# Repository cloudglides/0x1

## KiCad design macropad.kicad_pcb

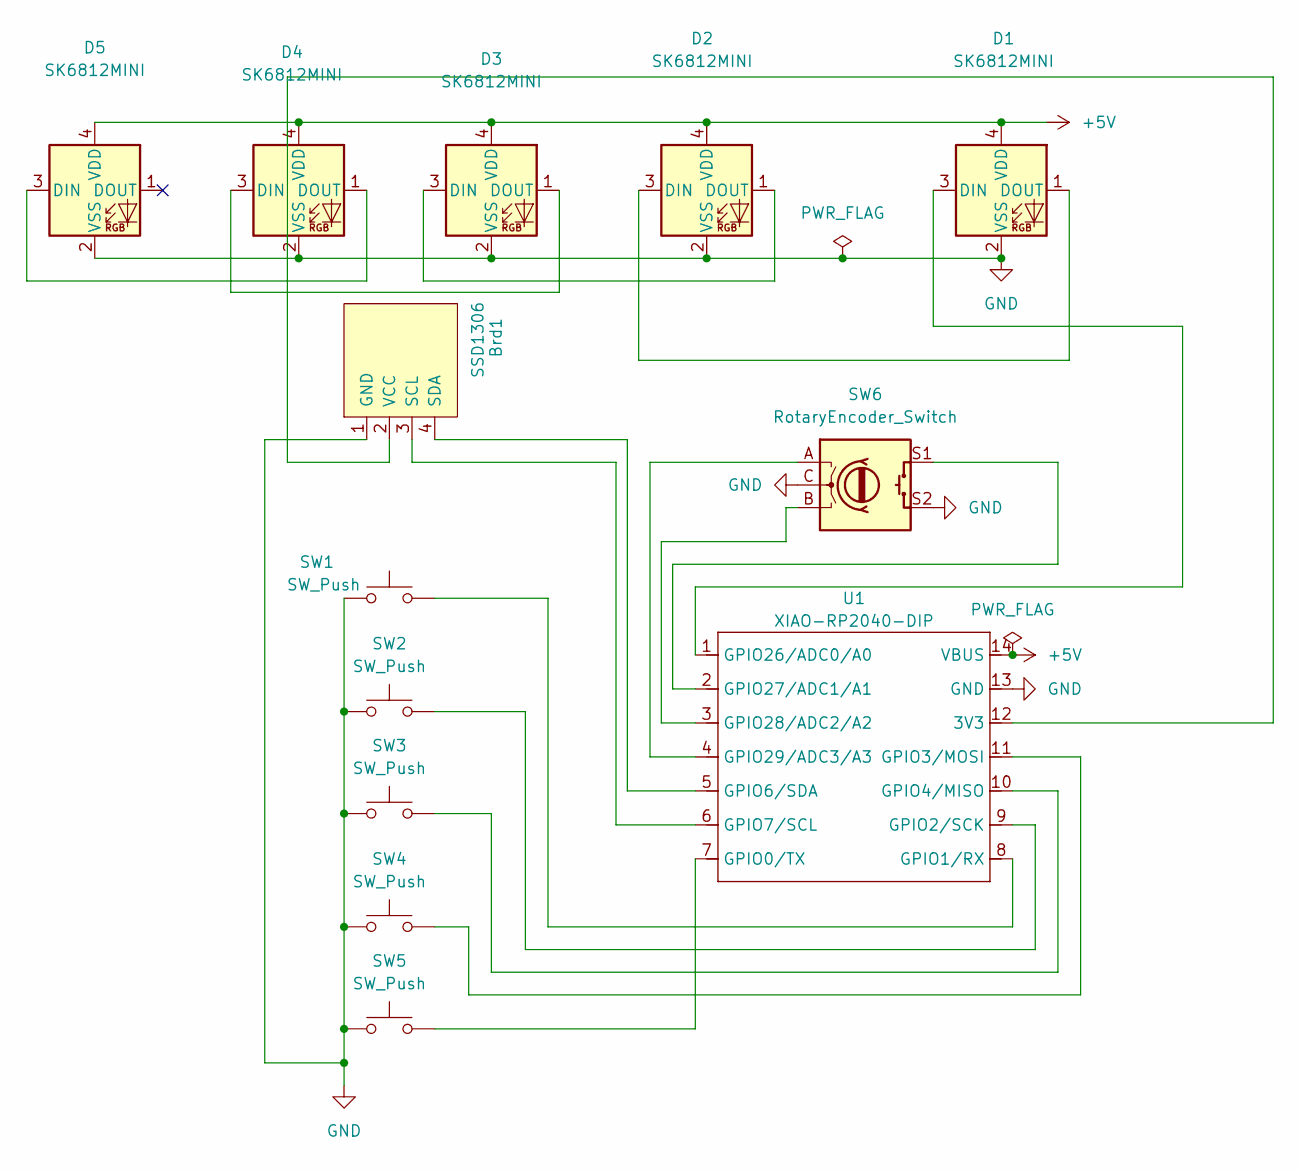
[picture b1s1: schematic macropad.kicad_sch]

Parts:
Brd1: SSD1306; SSD1306-0.91-OLED-4pin-128x32
D1, D2, D3, D4, D5: SK6812MINI; LED_SK6812MINI_PLCC4_3.5x3.5mm_P1.75mm
SW1, SW2, SW3, SW4, SW5: SW_Push; SW_Cherry_MX_1.00u_PCB
SW6: RotaryEncoder_Switch; RotaryEncoder_Alps_EC11E-Switch_Vertical_H20mm
U1: XIAO-RP2040-DIP

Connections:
+5V: D1.4 (VDD), D2.4 (VDD), D3.4 (VDD), D4.4 (VDD), D5.4 (VDD), U1.14 (VBUS)
GND: Brd1.1 (GND), D1.2 (VSS), D2.2 (VSS), D3.2 (VSS), D4.2 (VSS), D5.2 (VSS), SW1.1, SW2.1, SW3.1, SW4.1, SW5.1, SW6.C, SW6.S2, U1.13 (GND)
unnamed: Brd1.3 (SCL), U1.6 (GPIO7/SCL)
unnamed: Brd1.4 (SDA), U1.5 (GPIO6/SDA)
unnamed: Brd1.2 (VCC), U1.12 (3V3)
unnamed: D1.3 (DIN), U1.1 (GPIO26/ADC0/A0)
unnamed: D1.1 (DOUT), D2.3 (DIN)
unnamed: D2.1 (DOUT), D3.3 (DIN)
unnamed: D3.1 (DOUT), D4.3 (DIN)
unnamed: D4.1 (DOUT), D5.3 (DIN)
unnamed: SW5.2, U1.7 (GPIO0/TX)
unnamed: SW1.2, U1.8 (GPIO1/RX)
unnamed: SW2.2, U1.9 (GPIO2/SCK)
unnamed: SW4.2, U1.11 (GPIO3/MOSI)
unnamed: SW3.2, U1.10 (GPIO4/MISO)
unnamed: SW6.S1, U1.2 (GPIO27/ADC1/A1)
unnamed: SW6.B, U1.3 (GPIO28/ADC2/A2)
unnamed: SW6.A, U1.4 (GPIO29/ADC3/A3)

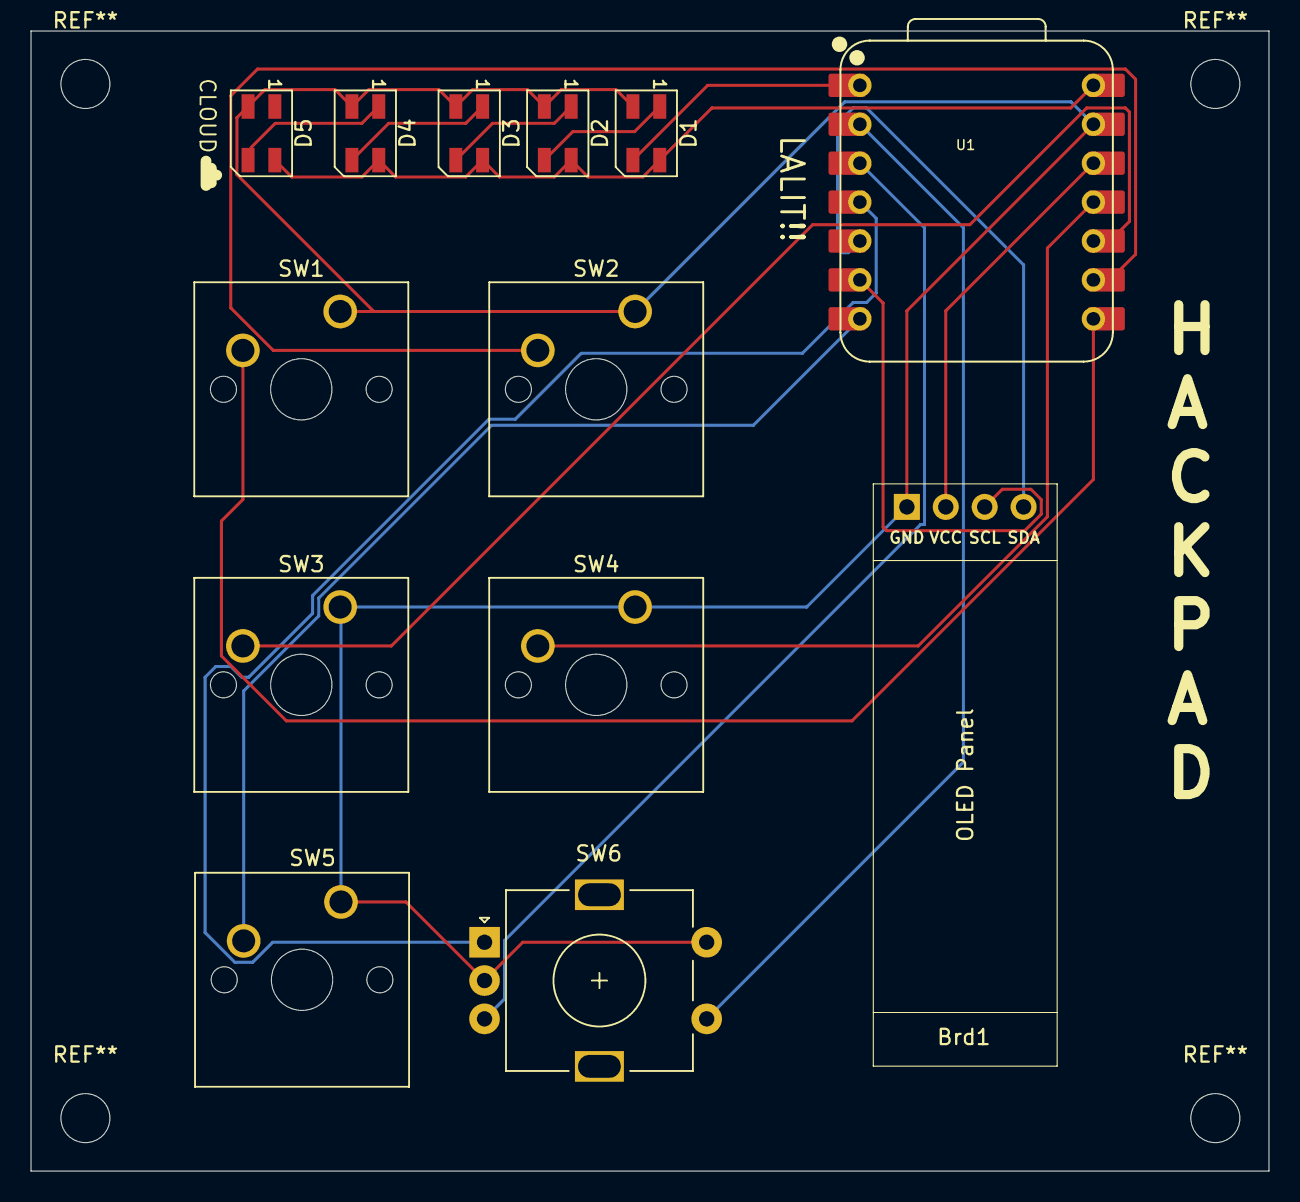
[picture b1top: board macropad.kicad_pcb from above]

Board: 2 copper layers, 80.8 x 74.4 mm, 13 parts (0 on the bottom side), 18 nets.

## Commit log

2025-12-06 init
2025-12-06 UPDATE:cleaning up
2025-12-09 UPDATE:added pcb case and other stuffz!!!
2025-12-09 update:added some preview images!!
2025-12-09 UPDATE:finalizing stuff
2025-12-09 UPDATE:readme stuff
2025-12-11 UPDATE: increased outer dia
2025-12-11 UPDATE: removed drl files
